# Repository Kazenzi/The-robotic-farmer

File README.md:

# 🚜 Decentralized Robotic Farming 🤖

Click the Youtube Thumbnail below for a youtube demo video: 
<div align="center">
  
</div>

## Overview

*Decentralized Robotic Farming* a.k.a "The Robotic Farmer" is an innovative solution that combines IoT technology and blockchain to enhance transparency, efficiency, and trust in agricultural practices. Our application enables real-time monitoring of farm conditions and automatic mechanized responses to address issues, all while securely storing farming data for easy access. The Robotic Farmer aims to improve crop yields, reduce resource wastage, and foster a more sustainable agricultural ecosystem.

Play with it live on: **[https://mkulima-welcome.vercel.app/](https://mkulima-welcome.vercel.app/)**

Our application applies the use of a smart contract deployed on the Base Mainnet. To verify, click [here](https://basescan.org/tx/0xa0cec8370d50e3738e3875305d2406a3c49cf04a951348cc5778b26b3b8fc69f) 

Proof that we have made 1+ transactions on Base for the project: [Transactions Made by mrsamuelkaruingi.base.eth](https://basescan.org/address/0xe854a712AE100D1089e1490179Ea1C1F786b56cc)

Contract Address: 0xcbb03c0470c16f5e1065cc8379252062e0d8d3d4

To explore further details, visit [BaseScan](https://basescan.org/) and paste the contract address above.

## <u>Table of Contents</u>
- [Problem Statement](#problem-statement)
- [Our Solution](#our-solution)
- [Key Features](#key-features)
- [Research Avenues](#research-avenues)
- [Installation](#installation)
- [Usage](#usage)
- [Future Enhancements](#future-enhancements)
- [Contributors](#contributors)
- [License](#license)

## Problem Statement

Agriculture today faces several challenges:
- Lack of trust and transparency between stakeholders.
- Absence of mechanized systems to respond to changing conditions.
- No proof of proper farming conditions, leading to wrongful accusations.
- Limited access to reliable, data-driven decision-making tools.

## Our Solution

We leverage IoT-enabled agriculture combined with Web 3 integration to create a robust platform for monitoring and managing farm conditions:
- *Real-time Monitoring*: Continuous data collection from various sensors.
- *Autonomous Robotics*: Implementation of robotic systems that autonomously perform tasks such as irrigation and fertilization based on real-time data.
- *Blockchain Storage*: Immutable records stored on IPFS, ensuring tamper-proof data.
- *Smart Contracts*: Automated updates and audits for all farm operations.

## Key Features

- *IoT Sensors*: Utilizes ultrasonic, soil temperature, water level, moisture, rainfall, and NPK sensors.
- *Automation*: Automatically manages irrigation and nutrient dosing based on real-time data.
- *Transparent Record-Keeping*: Immutable records on the blockchain provide legal protection for farmers.
- *Data Accessibility*: Stakeholders can access real-time data and historical records through an intuitive dashboard.

<div align="center">
    
</div>  

<br><br>

## Research Avenues
**1. Computer and Electrical/Electronics Engineering**

**2. Mechatronics and Robotics Engineering**

**3. Microprocessor Technology/ Embedded Systems** 

**4. Instrumentation and Control**

**5. Physics and Solar Energy**
   
<br>

Play with it live on: **[https://mkulima-welcome.vercel.app/](https://mkulima-welcome.vercel.app/)**

## Installation

**NOTE:** Code to control the hardware can be found in "mkulima_hardware/src". For IoT development strictly use equipment and documentation as specified. 

1. **Clone the Repository:**
   ```bash
   git clone https://github.com/Kazenzi/The-robotic-farmer.git
   cd The-robotic-farmer
   ```

2. **Install Dependencies:**
   ```bash
   npm install
   ```

   <br />

## Locally run

```sh
# Install bun in case you don't have it
curl -fsSL https://bun.sh/install | bash

# Install packages
bun i

# Run Next app
bun run dev
```
<br />

## Usage

1. **Run the Application:** Start the application by running:
   ```bash
   node index.js
   ```
   You will be prompted by your wallet (MetaMask or similar) to confirm the transaction for gas fees.
   As of the moment, the command will give you latest data from our testing phase but for more precise functionality, kindly use real sensors and connect the app to a bluetooth/wifi network to receive real-time data.
   
2. **Interact with the Smart Contract:**
   The `updateCID.js` script should update the IPFS CID for the latest sensor data automatically.
   - Confirm the transaction prompt when updating the CID.
   - You can use mock data to test the application if you do not have sensors.

The front end is fully functional and user-friendly. Ensure all necessary requirements are installed to run the app on your machine.
   
## Future Enhancements

- *Automatic Alerts*: Notifications for critical thresholds (e.g., low water levels).
- *Gas Fee Estimation*: Display gas fee estimates before transactions.
- *Offline Functionality*: Access sensor data offline.
- *Data Visualizations*: Implement charts for data trends over time to help farmers make informed decisions.

## Contributors

- [Samuel Njoroge](https://github.com/sammmmlikescoding)
- [Jacinta Kazenzi](https://github.com/Kazenzi)

## License

This project is licensed under the MIT License - see the [LICENSE](LICENSE) file for details.

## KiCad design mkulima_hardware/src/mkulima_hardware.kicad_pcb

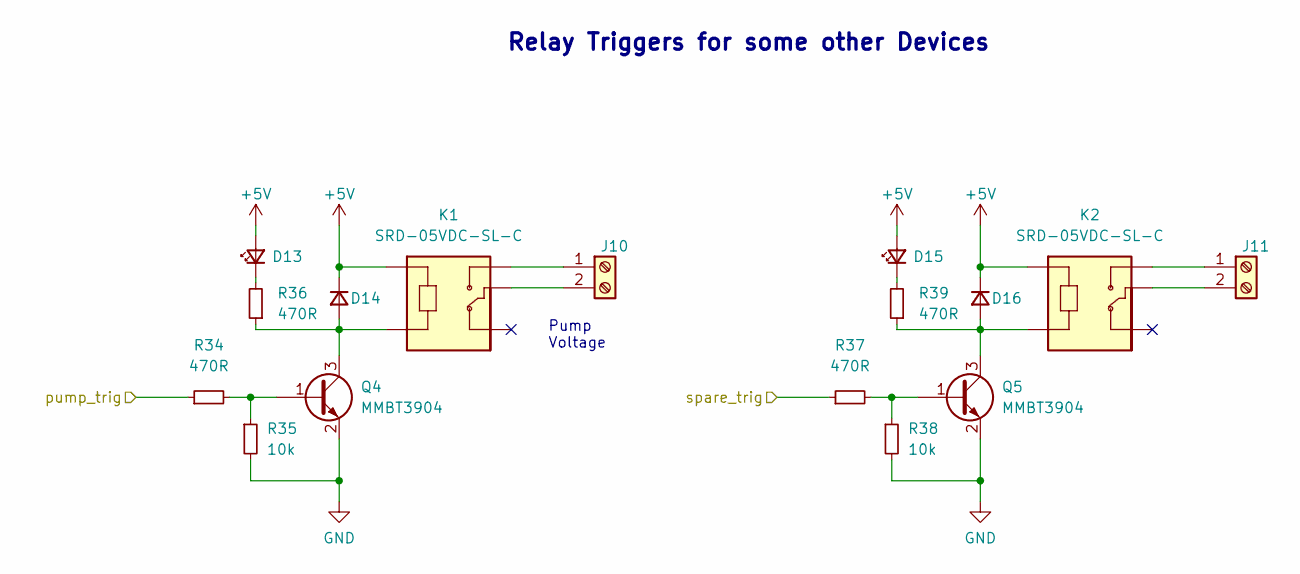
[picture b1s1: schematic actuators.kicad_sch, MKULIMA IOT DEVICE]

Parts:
D13, D15: LED_Small; LED_0805_2012Metric
D14, D16: D_Small; D_SOD-123
J10, J11: Screw_Terminal_01x02; TerminalBlock_Phoenix_PT-1,5-2-3.5-H_1x02_P3.50mm_Horizontal
K1, K2: SRD-05VDC-SL-C
Q4, Q5: MMBT3904; SOT-23
R34, R36, R37, R39: 470R; R_0805_2012Metric
R35, R38: 10k; R_0805_2012Metric

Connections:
+5V: D13.2 (A), D14.1 (K), D15.2 (A), D16.1 (K), K1.A1, K2.A1; also elsewhere on the board
/ESP32_logic_control/pumpTrig: R34.1; also elsewhere on the board
/ESP32_logic_control/spareTrig: R37.1; also elsewhere on the board
unnamed: D13.1 (K), R36.2
unnamed: D14.2 (A), K1.A2, Q4.3 (C), R36.1
unnamed: D15.1 (K), R39.2
unnamed: D16.2 (A), K2.A2, Q5.3 (C), R39.1
unnamed: J10.1, K1.NO
unnamed: J10.2, K1.COM
unnamed: J11.1, K2.NO
unnamed: J11.2, K2.COM
unnamed: Q4.1 (B), R34.2, R35.1
unnamed: Q5.1 (B), R37.2, R38.1

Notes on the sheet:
Relay Triggers for some other Devices
Pump Voltage

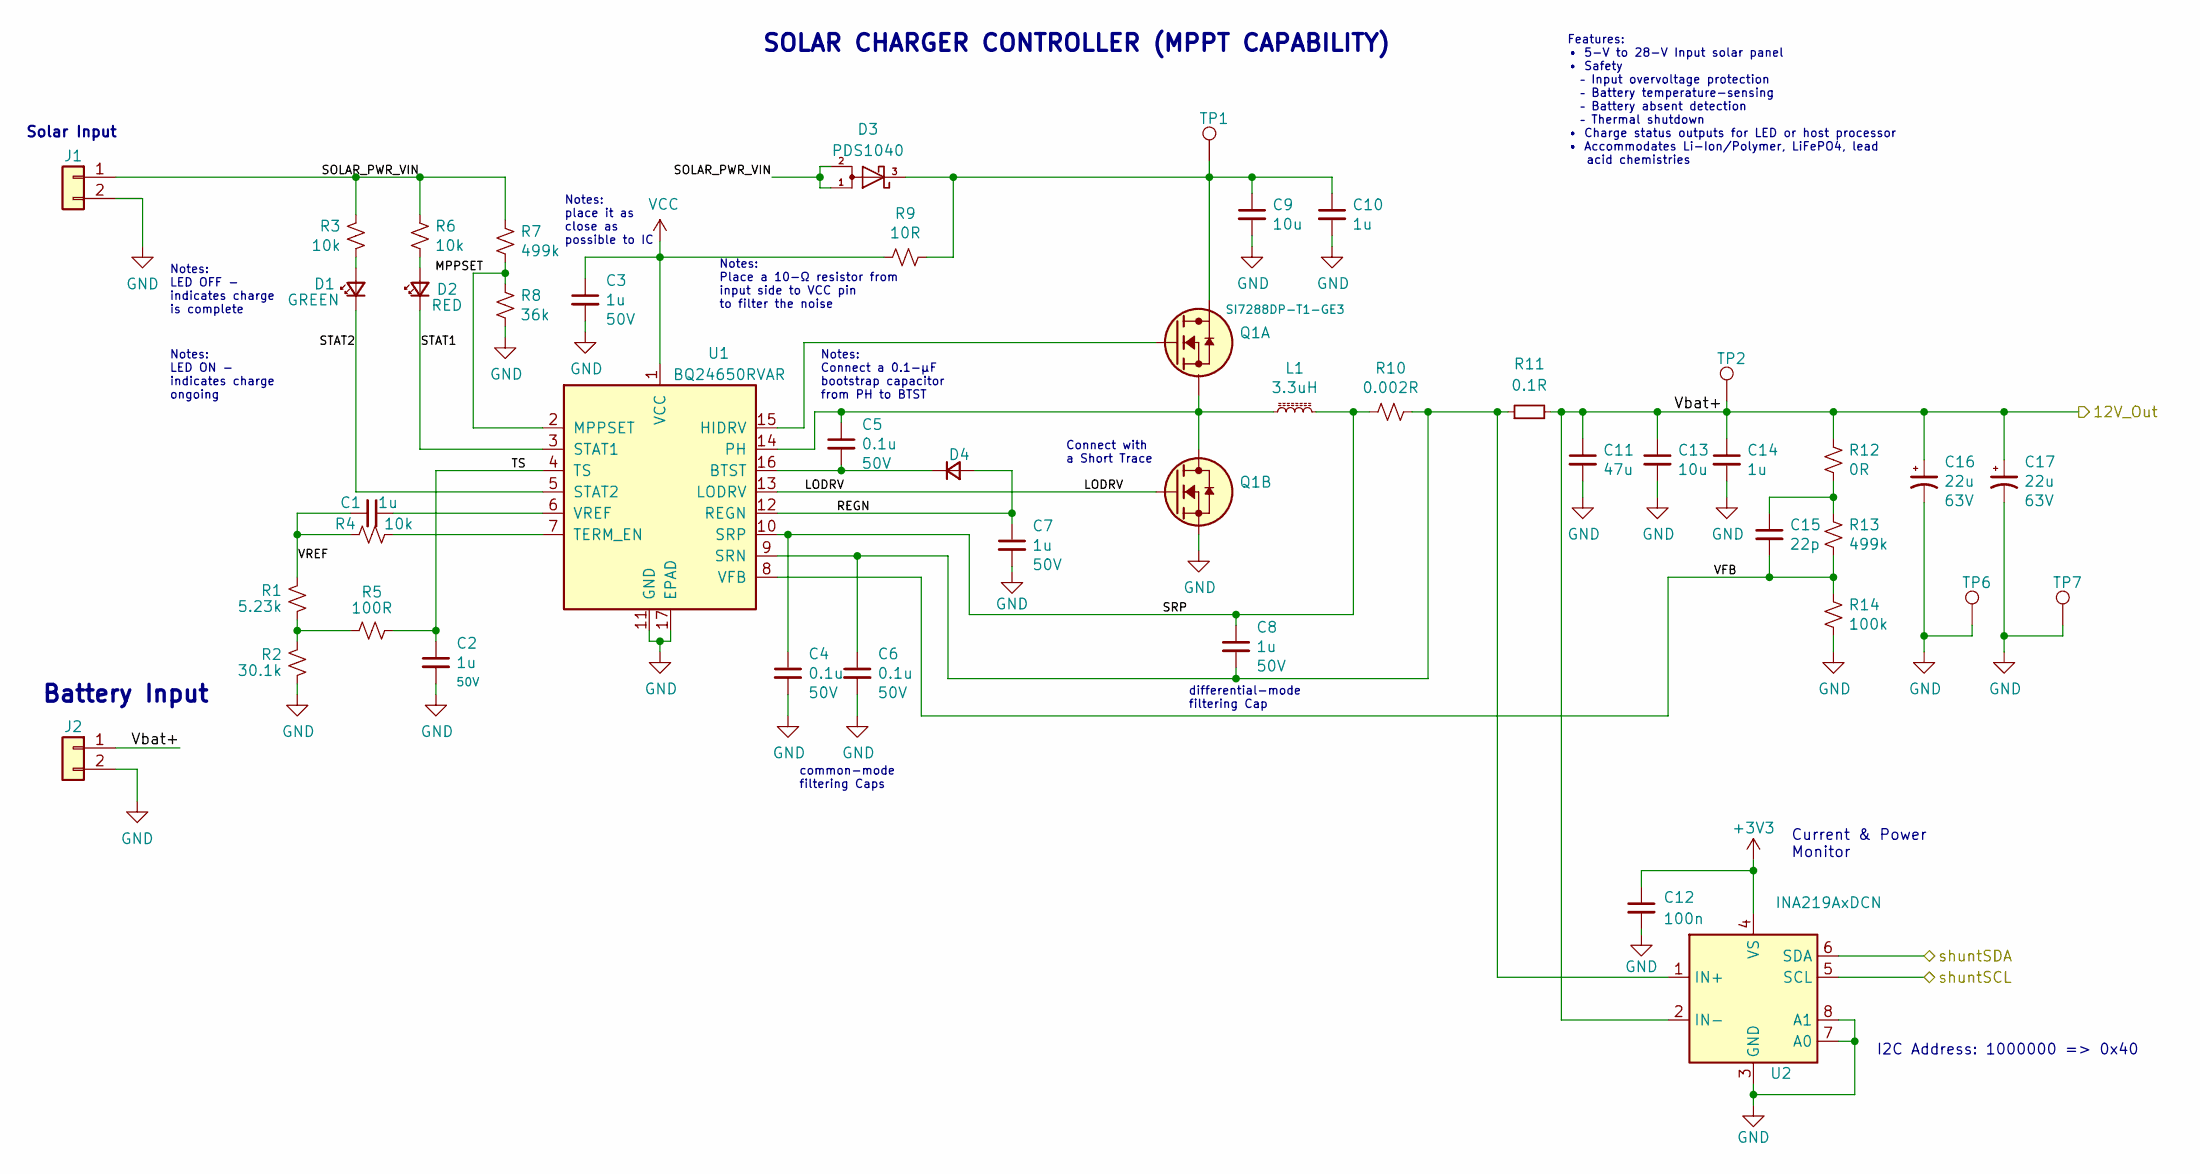
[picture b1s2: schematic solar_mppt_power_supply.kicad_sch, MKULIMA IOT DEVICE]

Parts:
C1, C10, C14: 1u; C_0805_2012Metric
C2, C3, C7, C8: 1u; C_0805_2012Metric; Voltage 50V
C4, C5, C6: 0.1u; C_0805_2012Metric; Voltage 50V
C9, C13: 10u; C_0805_2012Metric
C11: 47u; C_0805_2012Metric
C12: 100n; C_0805_2012Metric
C15: 22p; C_0805_2012Metric
C16, C17: 22u; CP_Elec_8x10; Voltage 63V; MPN VE-220M1JTR-0810
D1: GREEN; LED_0603_1608Metric
D2: RED; LED_0805_2012Metric
D3: PDS1040; PDS104013
D4: D_Small; D_SOD-323
J1, J2: Conn_01x02; TerminalBlock_Phoenix_PT-1,5-2-3.5-H_1x02_P3.50mm_Horizontal
L1: 3.3uH; MHCI06030-3R3M-R8; MPN MHCI06030-3R3M-R8
Q1: SI7288DP-T1-GE3; MPN SI7288DP-T1-GE3
R1: 5.23k; R_0805_2012Metric
R2: 30.1k; R_0805_2012Metric
R3, R4, R6: 10k; R_0805_2012Metric
R5: 100R; R_0805_2012Metric
R7, R13: 499k; R_0805_2012Metric
R8: 36k; R_0805_2012Metric
R9: 10R; R_0805_2012Metric
R10: 0.002R; R_0805_2012Metric
R11: 0.1R; R_0805_2012Metric
R12: 0R; R_0805_2012Metric
R14: 100k; R_0805_2012Metric
TP1, TP2, TP6, TP7: TestPoint; TestPoint_Pad_D1.5mm
U1: BQ24650RVAR
U2: INA219AxDCN; SOT-23-8

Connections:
+3V3: C12.1, U2.4 (VS); also elsewhere on the board
+12V: C11.1, C13.1, C14.1, C16.1, C17.1, J2.1, R11.2, R12.1, TP2.1, U2.2 (IN-); also elsewhere on the board
/scl: U2.5 (SCL); also elsewhere on the board
/sda: U2.6 (SDA); also elsewhere on the board
/solar_mppt_power_supply/LODRV: Q1.4, U1.13 (LODRV)
/solar_mppt_power_supply/MPPSET: R7.2, R8.1, U1.2 (MPPSET)
/solar_mppt_power_supply/REGN: C7.1, D4.2 (A), U1.12 (REGN)
/solar_mppt_power_supply/SOLAR_PWR_VIN: D3.1 (A), D3.2 (A), J1.1, R3.1, R6.1, R7.1
/solar_mppt_power_supply/SRP: C4.1, C8.1, L1.2, R10.2, U1.10 (SRP)
/solar_mppt_power_supply/STAT1: D2.1 (K), U1.3 (STAT1)
/solar_mppt_power_supply/STAT2: D1.1 (K), U1.5 (STAT2)
/solar_mppt_power_supply/TS: C2.1, R5.1, U1.4 (TS)
/solar_mppt_power_supply/VFB: C15.2, R13.2, R14.1, U1.8 (VFB)
/solar_mppt_power_supply/VREF: C1.2, R1.1, R4.2
unnamed: C1.1, U1.6 (VREF)
unnamed: C5.1, L1.1, Q1.1, Q1.5, Q1.6, Q1.10, U1.14 (PH)
unnamed: C5.2, D4.1 (K), U1.16 (BTST)
unnamed: C6.1, C8.2, R10.1, R11.1, U1.9 (SRN), U2.1 (IN+)
unnamed: C9.1, C10.1, D3.3 (K), Q1.7, Q1.8, Q1.9, R9.1, TP1.1
unnamed: C15.1, R12.2, R13.1
unnamed: D1.2 (A), R3.2
unnamed: D2.2 (A), R6.2
unnamed: Q1.2, U1.15 (HIDRV)
unnamed: R1.2, R2.1, R5.2
unnamed: R4.1, U1.7 (TERM_EN)
VCC: C3.1, R9.2, U1.1 (VCC)

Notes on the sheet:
Notes: Place a 10-Ω resistor from input side to VCC pin to filter the noise
differential-mode filtering Cap
Features: • 5-V to 28-V Input solar panel • Safety – Input overvoltage protection – Battery temperature-sensing – Battery absent detection – Thermal shutdown • Charge status outputs for LED or host processor • Accommodates Li-Ion/Polymer, LiFePO4, lead acid chemistries
Notes: LED OFF - indicates charge is complete
Solar Input
Notes: Connect a 0.1-μF bootstrap capacitor from PH to BTST
Notes: LED ON - indicates charge ongoing
Connect with a Short Trace
Current & Power Monitor
Notes: place it as close as possible to IC
common-mode filtering Caps
Battery Input
SOLAR CHARGER CONTROLLER (MPPT CAPABILITY)
I2C Address: 1000000 => 0x40

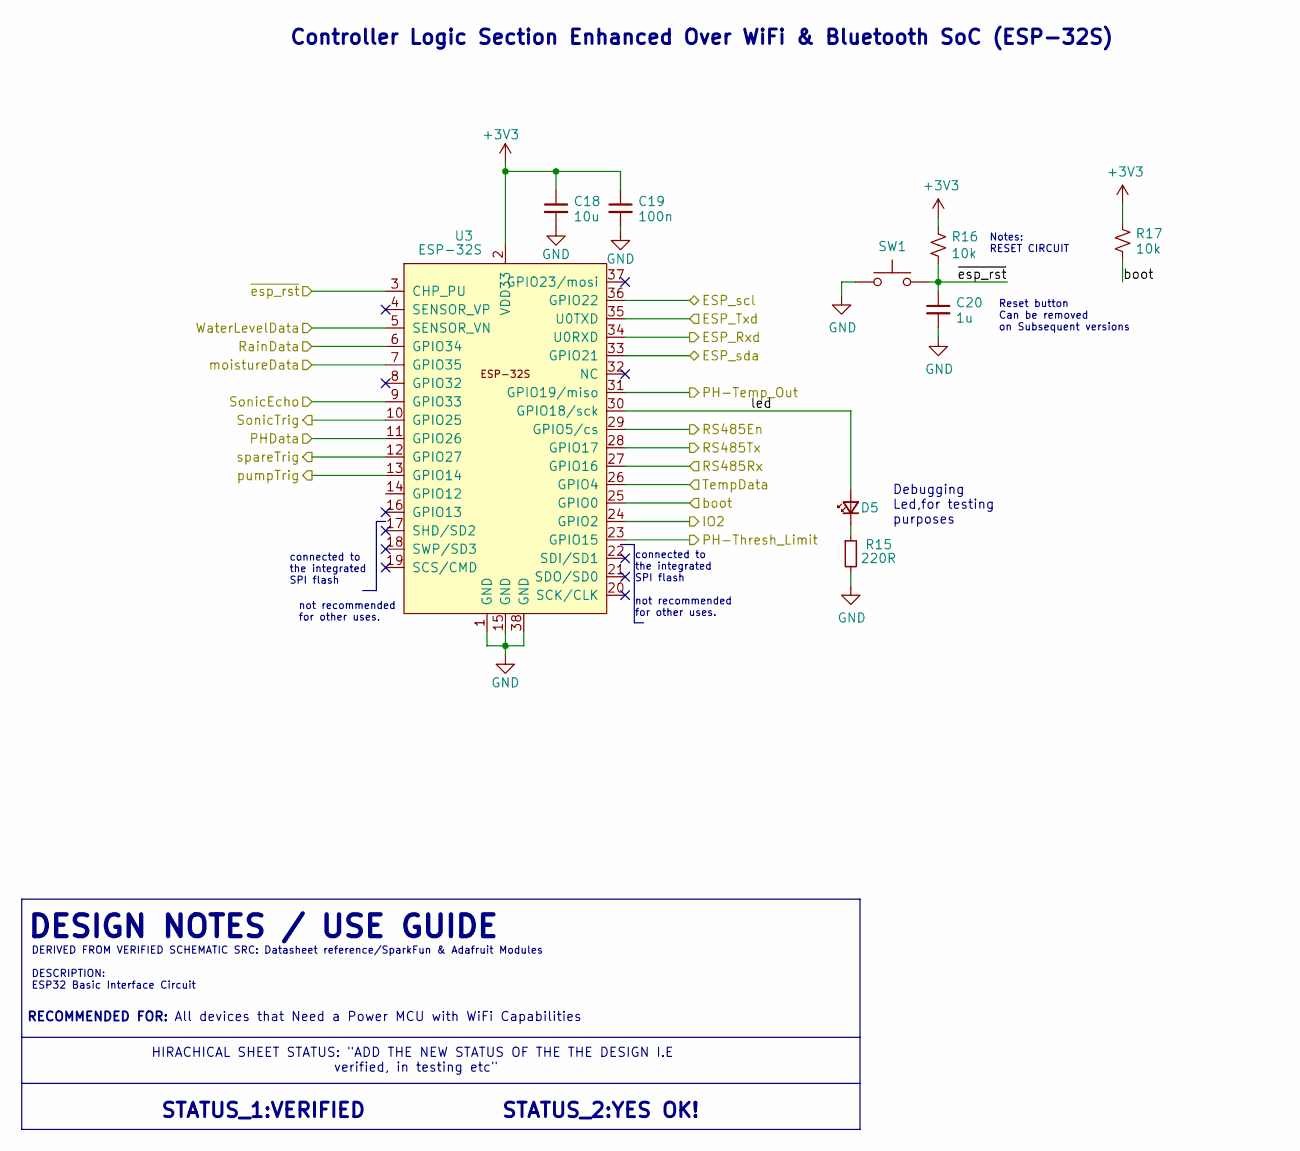
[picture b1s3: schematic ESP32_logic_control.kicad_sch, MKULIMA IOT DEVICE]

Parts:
C18: 10u; C_0805_2012Metric
C19: 100n; C_0805_2012Metric
C20: 1u; C_0805_2012Metric
D5: LED_Small; LED_0805_2012Metric
R15: 220R; R_0805_2012Metric
R16, R17: 10k; R_0805_2012Metric
SW1: SW_Push; SKRPACE010
U3: ESP-32S

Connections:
+3V3: C18.1, C19.1, R16.1, R17.1, U3.2 (VDD33); also elsewhere on the board
/ESP32_logic_control/ESP_Rxd: U3.34 (U0RXD); also elsewhere on the board
/ESP32_logic_control/ESP_Txd: U3.35 (U0TXD); also elsewhere on the board
/ESP32_logic_control/IO2: U3.24 (GPIO2); also elsewhere on the board
/ESP32_logic_control/PH-Temp_Out: U3.31 (GPIO19/miso); also elsewhere on the board
/ESP32_logic_control/PH-Thresh_Limit: U3.23 (GPIO15); also elsewhere on the board
/ESP32_logic_control/PHData: U3.11 (GPIO26); also elsewhere on the board
/ESP32_logic_control/RS485En: U3.29 (GPIO5/cs); also elsewhere on the board
/ESP32_logic_control/RS485Rx: U3.27 (GPIO16); also elsewhere on the board
/ESP32_logic_control/RS485Tx: U3.28 (GPIO17); also elsewhere on the board
/ESP32_logic_control/RainData: U3.6 (GPIO34); also elsewhere on the board
/ESP32_logic_control/SonicEcho: U3.9 (GPIO33); also elsewhere on the board
/ESP32_logic_control/SonicTrig: U3.10 (GPIO25); also elsewhere on the board
/ESP32_logic_control/TempData: U3.26 (GPIO4); also elsewhere on the board
/ESP32_logic_control/WaterLevelData: U3.5 (SENSOR_VN); also elsewhere on the board
/ESP32_logic_control/boot: R17.2, U3.25 (GPIO0); also elsewhere on the board
/ESP32_logic_control/led: D5.2 (A), U3.30 (GPIO18/sck)
/ESP32_logic_control/moistureData: U3.7 (GPIO35); also elsewhere on the board
/ESP32_logic_control/pumpTrig: U3.13 (GPIO14); also elsewhere on the board
/ESP32_logic_control/spareTrig: U3.12 (GPIO27); also elsewhere on the board
/ESP32_logic_control/~esp_rst: C20.1, R16.2, SW1.2, U3.3 (CHP_PU); also elsewhere on the board
/scl: U3.36 (GPIO22); also elsewhere on the board
/sda: U3.33 (GPIO21); also elsewhere on the board
unnamed: D5.1 (K), R15.1

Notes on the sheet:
STATUS_2:YES OK!
STATUS_1:VERIFIED
Debugging Led,for testing purposes
Reset button Can be removed on Subsequent versions
DERIVED FROM VERIFIED SCHEMATIC SRC: Datasheet reference/SparkFun & Adafruit Modules DESCRIPTION: ESP32 Basic Interface Circuit
not recommended for other uses.
DESIGN NOTES / USE GUIDE
HIRACHICAL SHEET STATUS: "ADD THE NEW STATUS OF THE THE DESIGN I.E verified, in testing etc"
Controller Logic Section Enhanced Over WiFi & Bluetooth SoC (ESP-32S)
connected to the integrated SPI flash
All devices that Need a Power MCU with WiFi Capabilities
connected to the integrated SPI flash not recommended for other uses.
Notes: RESET CIRCUIT
RECOMMENDED FOR:

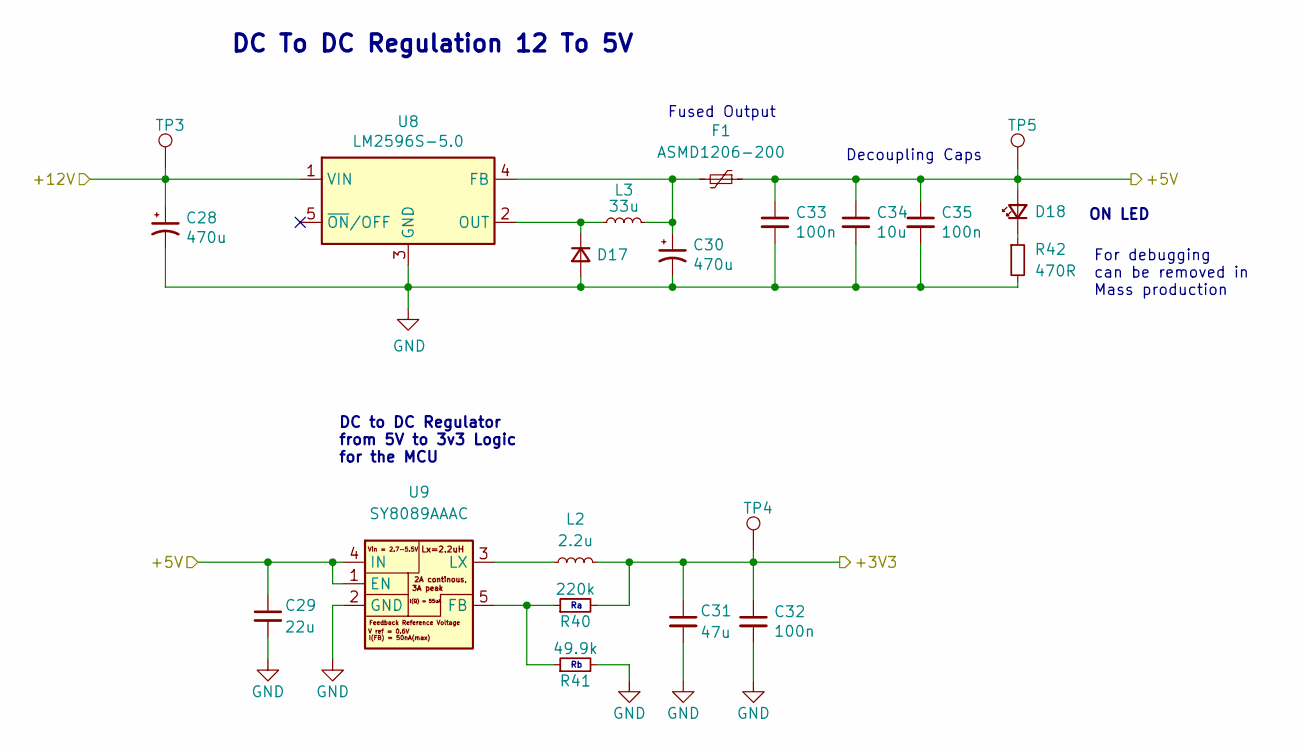
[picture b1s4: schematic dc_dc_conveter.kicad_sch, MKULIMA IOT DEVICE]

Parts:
C28, C30: 470u; CP_Elec_6.3x7.7; Mfr# UTOJ471M0607VG
C29: 22u; C_0805_2012Metric
C31: 47u; C_0805_2012Metric
C32, C33, C35: 100n; C_0805_2012Metric
C34: 10u; C_0805_2012Metric
D17: D_Small; D_SMC
D18: LED_Small; LED_0805_2012Metric
F1: ASMD1206-200; Fuse_1206_3216Metric; Mfr# ASMD1206-200
L2: 2.2u; NR3015T2R2M; Mfr# NR3015T2R2M
L3: 33u; YSPI1050-xxx
R40: 220k; R_0805_2012Metric
R41: 49.9k; R_0805_2012Metric
R42: 470R; R_0805_2012Metric
TP3, TP4, TP5: TestPoint; TestPoint_Pad_D1.5mm
U8: LM2596S-5.0; TO-263-5_TabPin3
U9: SY8089AAAC; SOT-23-5

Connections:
+3V3: C31.1, C32.1, L2.2, R40.2, TP4.1; also elsewhere on the board
+5V: C29.1, C33.1, C34.1, C35.1, D18.2 (A), F1.1, TP5.1, U9.1 (EN), U9.4 (IN); also elsewhere on the board
+12V: C28.1, TP3.1, U8.1 (VIN); also elsewhere on the board
unnamed: C30.1, F1.2, L3.2, U8.4 (FB)
unnamed: D17.1 (K), L3.1, U8.2 (OUT)
unnamed: D18.1 (K), R42.1
unnamed: L2.1, U9.3 (LX)
unnamed: R40.1, R41.1, U9.5 (FB)

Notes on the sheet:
DC To DC Regulation 12 To 5V
DC to DC Regulator from 5V to 3v3 Logic for the MCU
Fused Output
ON LED
Decoupling Caps
For debugging can be removed in Mass production

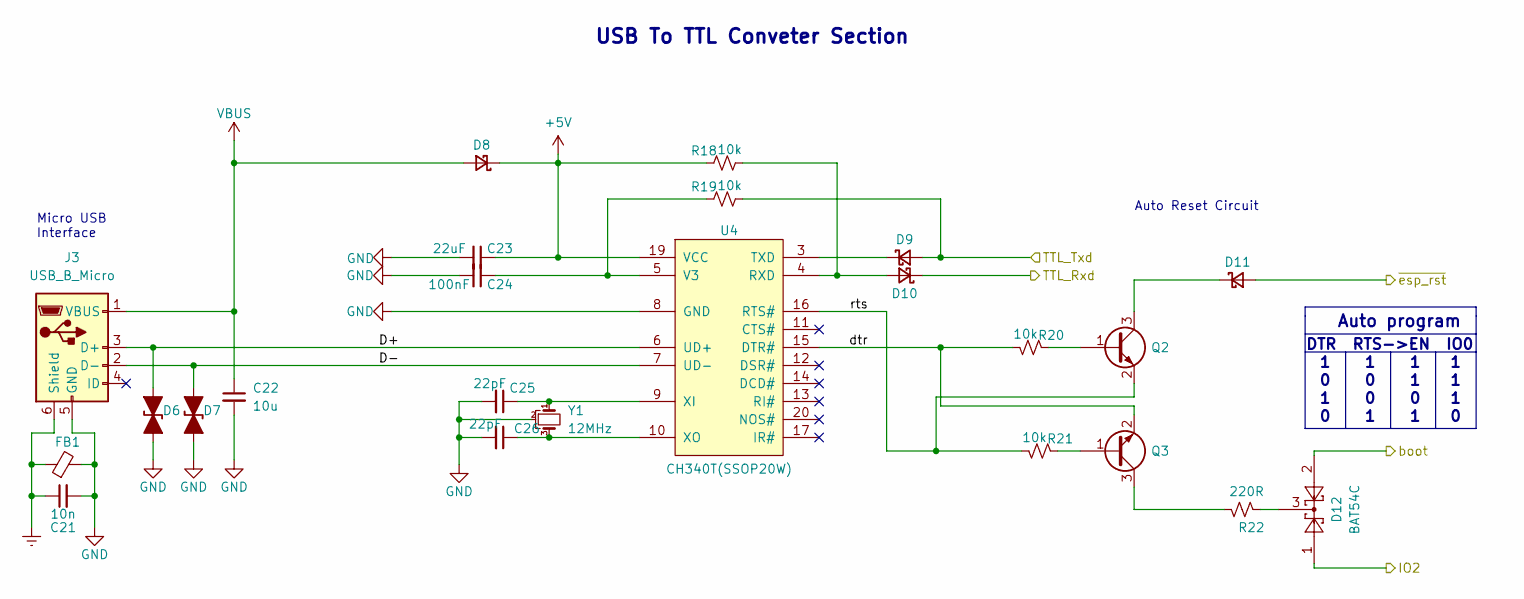
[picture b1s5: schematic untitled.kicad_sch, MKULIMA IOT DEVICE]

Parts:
C21: 10n; C_0805_2012Metric
C22: 10u; C_0805_2012Metric
C23: 22uF; C_0805_2012Metric
C24: 100nF; C_0805_2012Metric
C25, C26: 22pF; C_0805_2012Metric
D6, D7: D_TVS_Filled; D_SOD-923; Mfr# ESD9B5.0ST5G
D8: D_Schottky_Small; D_SOD-123
D9, D10, D11: B5819W; D_SOD-123
D12: BAT54C; SOT-23
FB1: FerriteBead_Small; L_0603_1608Metric
J3: USB_B_Micro; USB_Micro-B_Molex-105017-0001
Q2, Q3: MMBT3904; SOT-23
R18, R19, R20, R21: 10k; R_0805_2012Metric
R22: 220R; R_0805_2012Metric
U4: CH340T(SSOP20W); SSOP-20_5.3x7.2mm_P0.65mm
Y1: 12MHz; Crystal_SMD_2520-4Pin_2.5x2.0mm

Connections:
+5V: C23.1, D8.1 (K), R18.1, U4.19 (VCC); also elsewhere on the board
/ESP32_logic_control/ESP_Rxd: D9.2 (A), R19.2; also elsewhere on the board
/ESP32_logic_control/ESP_Txd: D10.1 (K); also elsewhere on the board
/ESP32_logic_control/IO2: D12.1; also elsewhere on the board
/ESP32_logic_control/boot: D12.2; also elsewhere on the board
/ESP32_logic_control/~esp_rst: D11.2 (A); also elsewhere on the board
/usb_to_uart_converter/D+: D6.2 (A2), J3.3 (D+), U4.6 (UD+)
/usb_to_uart_converter/D-: D7.2 (A2), J3.2 (D-), U4.7 (UD-)
/usb_to_uart_converter/dtr: Q3.2 (E), R20.2, U4.15 (DTR#)
/usb_to_uart_converter/rts: Q2.2 (E), R21.2, U4.16 (RTS#)
Earth: C21.1, FB1.1, J3.6 (Shield)
unnamed: C24.1, R19.1, U4.5 (V3)
unnamed: C25.1, U4.9 (XI), Y1.1
unnamed: C26.1, U4.10 (XO), Y1.3
unnamed: D9.1 (K), U4.3 (TXD)
unnamed: D10.2 (A), R18.2, U4.4 (RXD)
unnamed: D11.1 (K), Q2.3 (C)
unnamed: D12.3, R22.1
unnamed: Q2.1 (B), R20.1
unnamed: Q3.1 (B), R21.1
unnamed: Q3.3 (C), R22.2
VBUS: C22.1, D8.2 (A), J3.1 (VBUS)

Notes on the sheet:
Auto program
DTR RTS->EN IO0
USB To TTL Conveter Section
Auto Reset Circuit
Micro USB Interface

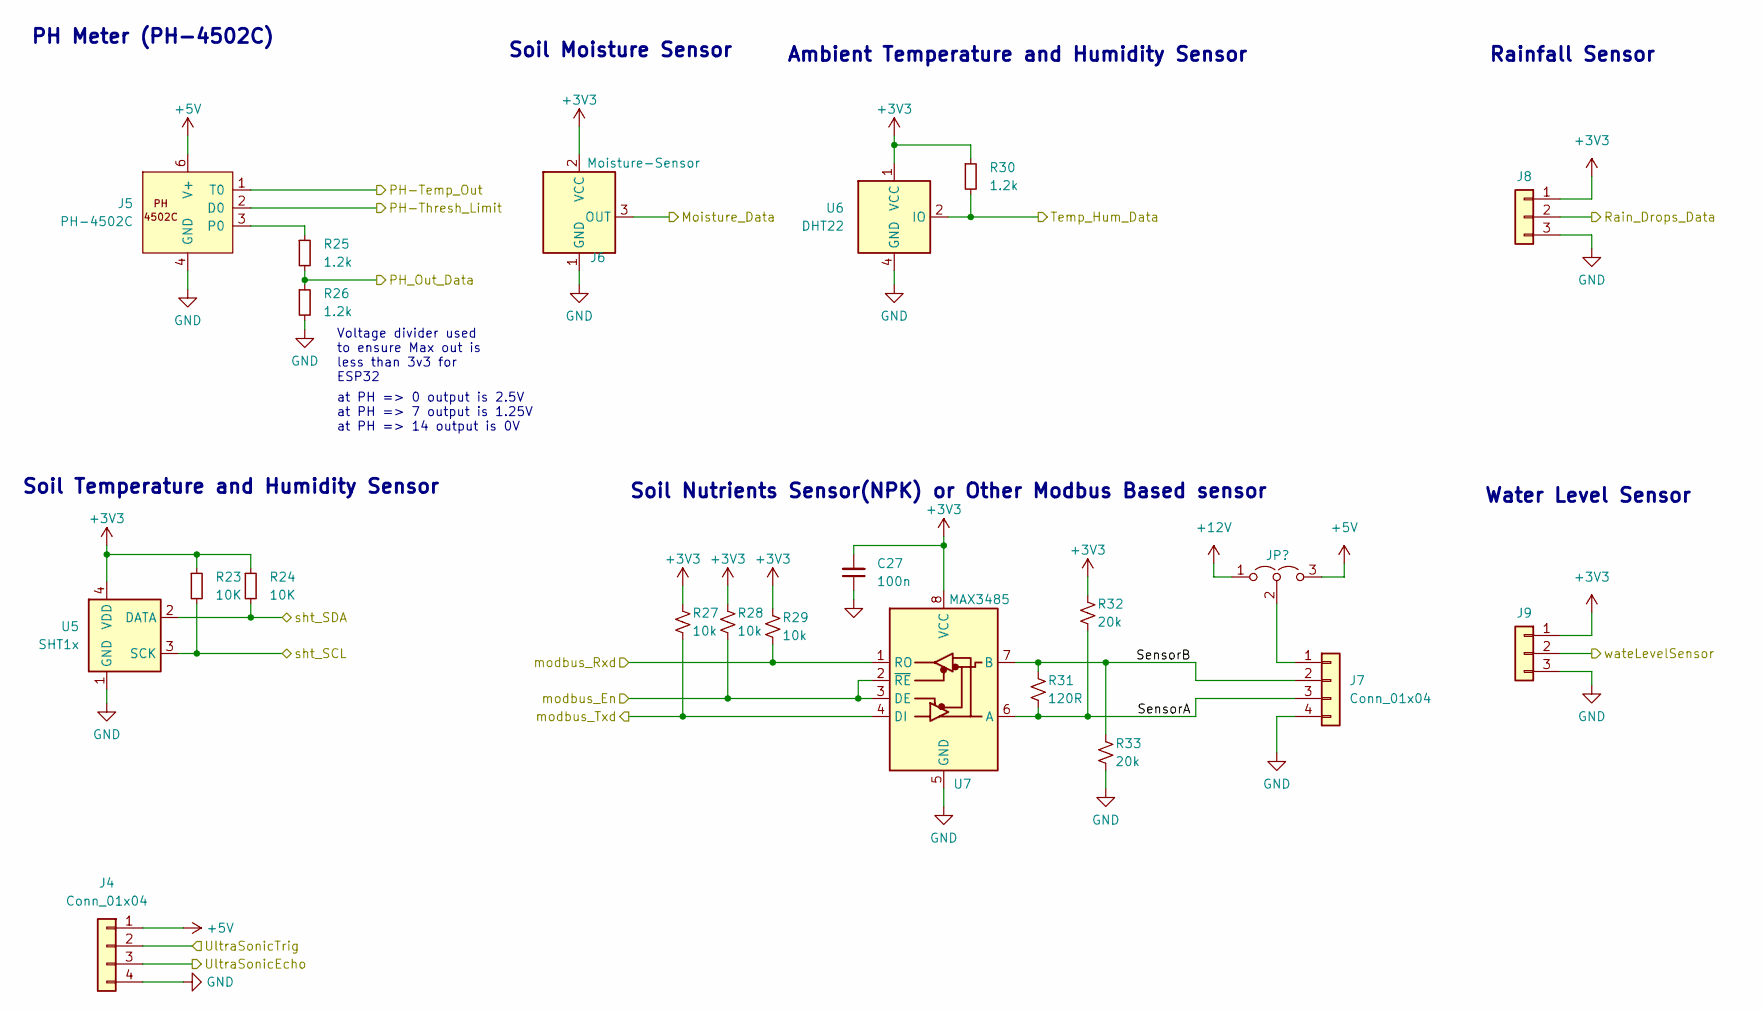
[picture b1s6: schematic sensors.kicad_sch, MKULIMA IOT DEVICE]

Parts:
C27: 100n; C_0805_2012Metric
J4, J7: Conn_01x04; TerminalBlock_Phoenix_MPT-0,5-4-2.54_1x04_P2.54mm_Horizontal
J5: PH-4502C
J6: Moisture-Sensor; TerminalBlock_Phoenix_MPT-0,5-3-2.54_1x03_P2.54mm_Horizontal
J8, J9: Conn_01x03; TerminalBlock_Phoenix_MPT-0,5-3-2.54_1x03_P2.54mm_Horizontal
R23, R24: 10K; R_0805_2012Metric
R25, R26, R30: 1.2k; R_0805_2012Metric
R27, R28, R29: 10k; R_0805_2012Metric
R31: 120R; R_0805_2012Metric
R32, R33: 20k; R_0805_2012Metric
U5: SHT1x; TerminalBlock_Phoenix_MPT-0,5-4-2.54_1x04_P2.54mm_Horizontal
U6: DHT22; TerminalBlock_Phoenix_MPT-0,5-4-2.54_1x04_P2.54mm_Horizontal
U7: MAX3485; SOP-8_3.9x4.9mm_P1.27mm

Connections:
+3V3: C27.2, J6.2 (VCC), J8.1, J9.1, R23.1, R24.1, R27.1, R28.1, R29.1, R30.1, R32.1, U5.4 (VDD), U6.1 (VCC), U7.8 (VCC); also elsewhere on the board
+5V: J4.1, J5.6 (V+); also elsewhere on the board
+12V: J7.1; also elsewhere on the board
/ESP32_logic_control/PH-Temp_Out: J5.1 (T0); also elsewhere on the board
/ESP32_logic_control/PH-Thresh_Limit: J5.2 (D0); also elsewhere on the board
/ESP32_logic_control/PHData: R25.2, R26.1; also elsewhere on the board
/ESP32_logic_control/RS485En: R28.2, U7.2 (~RE), U7.3 (DE); also elsewhere on the board
/ESP32_logic_control/RS485Rx: R27.2, U7.4 (DI); also elsewhere on the board
/ESP32_logic_control/RS485Tx: R29.2, U7.1 (RO); also elsewhere on the board
/ESP32_logic_control/RainData: J8.2; also elsewhere on the board
/ESP32_logic_control/SonicEcho: J4.3; also elsewhere on the board
/ESP32_logic_control/SonicTrig: J4.2; also elsewhere on the board
/ESP32_logic_control/TempData: R30.2, U6.2 (IO); also elsewhere on the board
/ESP32_logic_control/WaterLevelData: J9.2; also elsewhere on the board
/ESP32_logic_control/moistureData: J6.3 (OUT); also elsewhere on the board
/scl: R23.2, U5.3 (SCK); also elsewhere on the board
/sda: R24.2, U5.2 (DATA); also elsewhere on the board
/sensors/SensorA: J7.3, R31.2, R32.2, U7.6 (A)
/sensors/SensorB: J7.2, R31.1, R33.1, U7.7 (B)
unnamed: J5.3 (P0), R25.1

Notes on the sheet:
Water Level Sensor
Rainfall Sensor
at PH => 0 output is 2.5V at PH => 7 output is 1.25V at PH => 14 output is 0V
Ambient Temperature and Humidity Sensor
Soil Temperature and Humidity Sensor
PH Meter (PH-4502C)
Soil Moisture Sensor
Voltage divider used to ensure Max out is less than 3v3 for ESP32
Soil Nutrients Sensor(NPK) or Other Modbus Based sensor

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
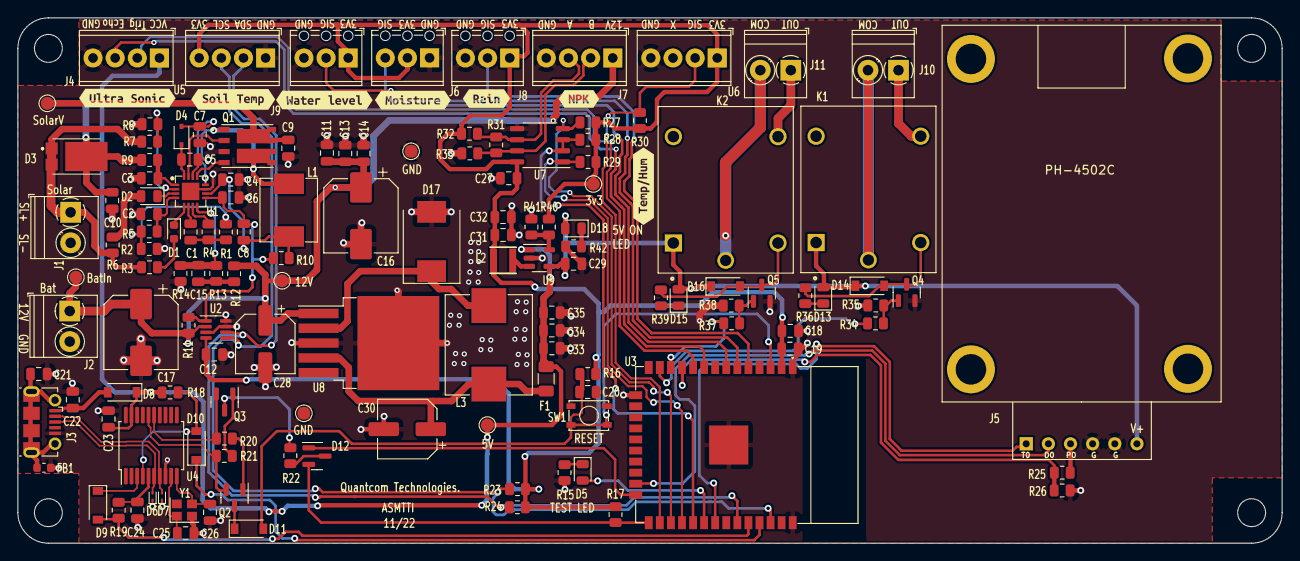
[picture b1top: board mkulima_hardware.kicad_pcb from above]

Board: 2 copper layers, 145.0 x 60.2 mm, 143 parts (0 on the bottom side), 83 nets.

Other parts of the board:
kibuzzard-63678A0A: G***; kibuzzard-63678A0A
kibuzzard-63678A18: G***; kibuzzard-63678A18
kibuzzard-63678A29: G***; kibuzzard-63678A29
kibuzzard-636789D9: G***; kibuzzard-636789D9
kibuzzard-636789EB: G***; kibuzzard-636789EB
kibuzzard-636789FE: G***; kibuzzard-636789FE
kibuzzard-6367899D: G***; kibuzzard-6367899D

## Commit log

2024-10-13 ipfs
2024-10-15 Rename updateCID.js to updateCID.cjs
2024-10-19 Add IoT files via upload
2024-10-19 Add images
2024-10-22 Rename mkulima_hardware_side.png to hardware_side.png
2024-10-22 Rename mkulima_hardware_page-0005.jpg to IoT-skeleton-setup.jpg
2024-10-22 Rename mkulima_hardware_top.png to hardware_top.png
2024-10-22 Rename raw.jpeg to board.jpeg
